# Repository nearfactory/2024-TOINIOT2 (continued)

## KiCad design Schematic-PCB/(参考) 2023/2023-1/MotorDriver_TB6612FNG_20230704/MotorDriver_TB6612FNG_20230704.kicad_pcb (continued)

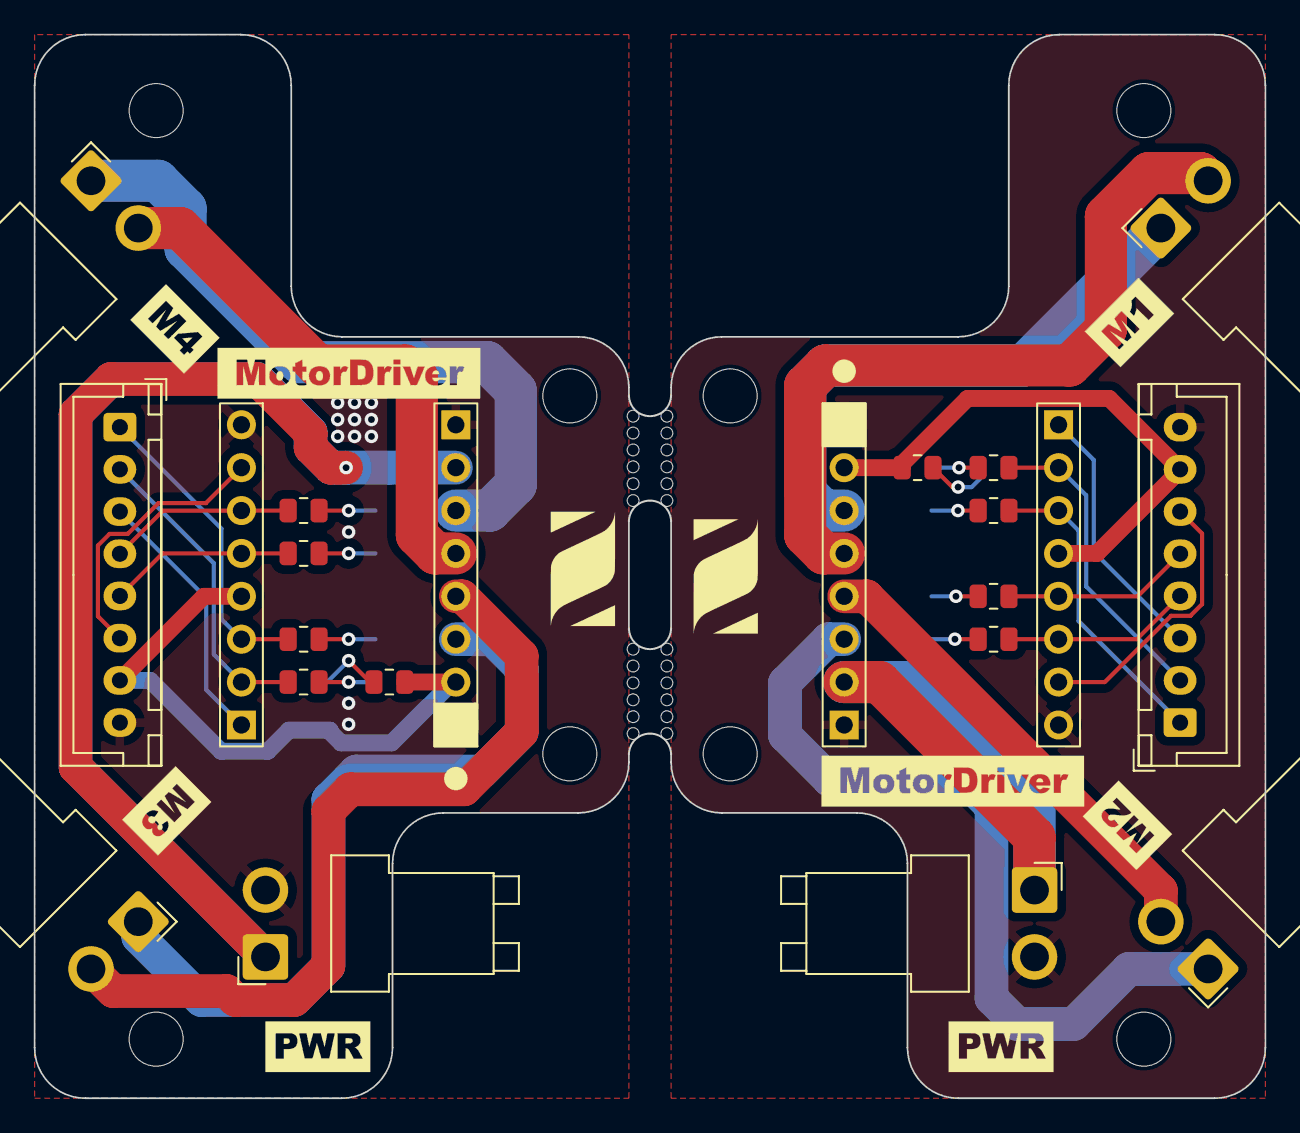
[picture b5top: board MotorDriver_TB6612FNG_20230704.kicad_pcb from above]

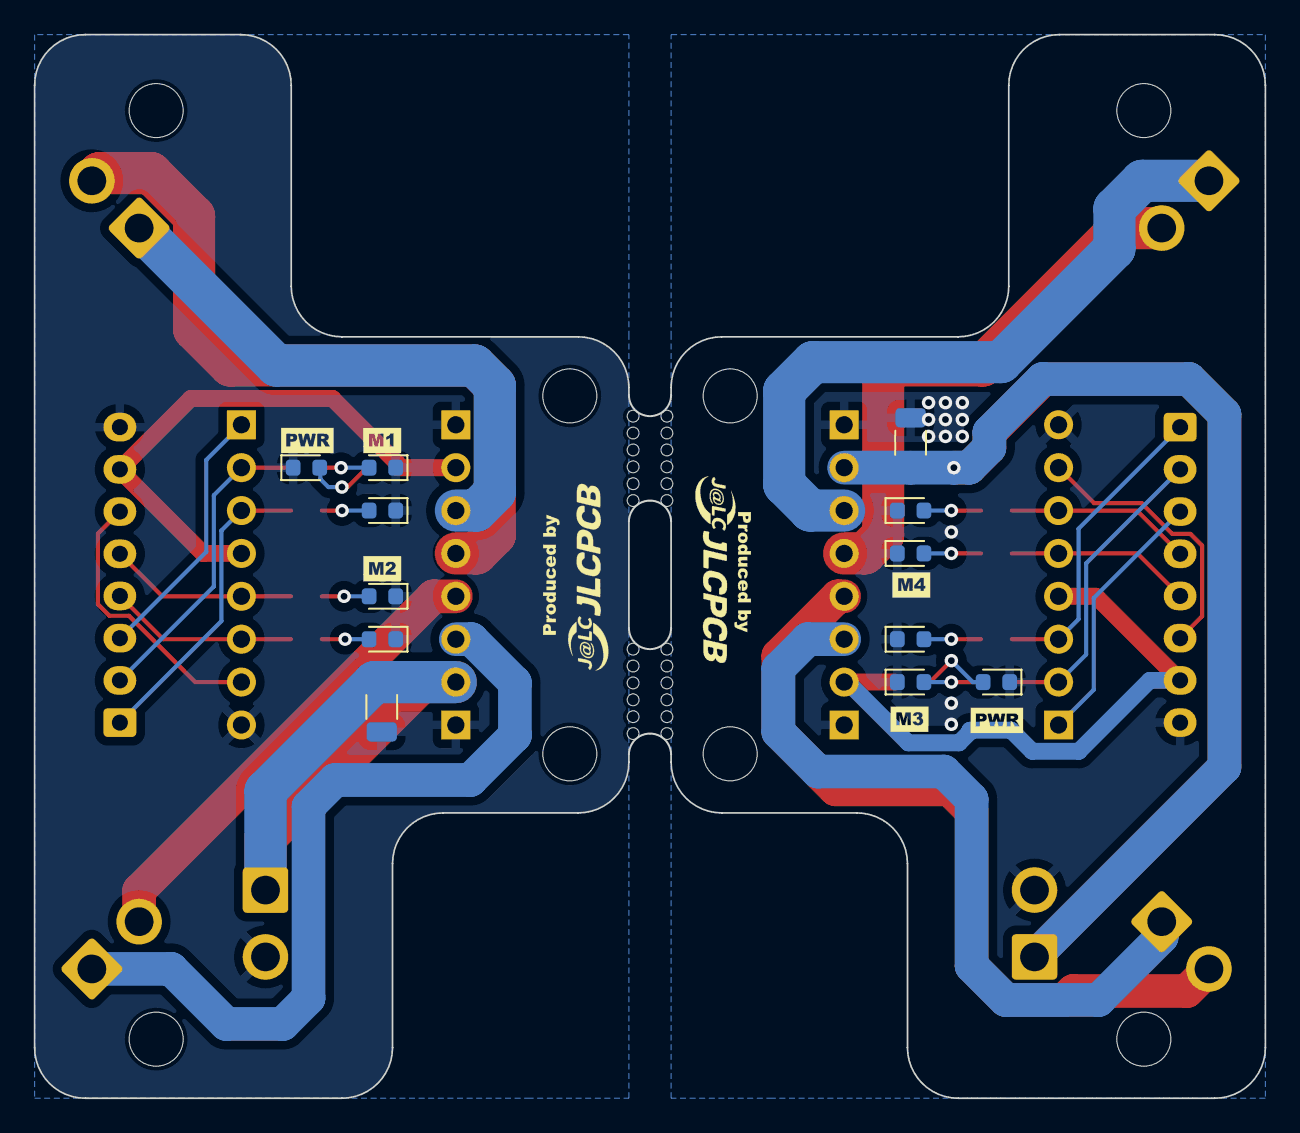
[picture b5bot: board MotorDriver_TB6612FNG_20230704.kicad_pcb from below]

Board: 2 copper layers, 72.9 x 63.0 mm, 32 parts (12 on the bottom side), 35 nets.

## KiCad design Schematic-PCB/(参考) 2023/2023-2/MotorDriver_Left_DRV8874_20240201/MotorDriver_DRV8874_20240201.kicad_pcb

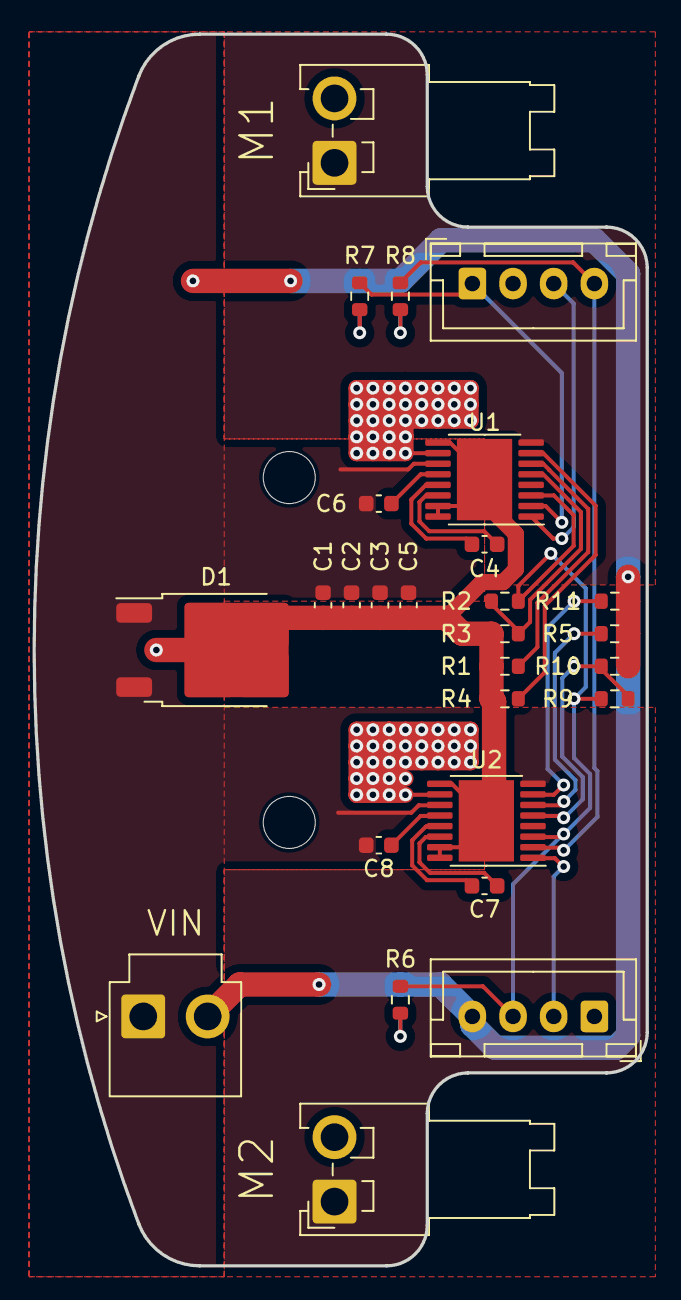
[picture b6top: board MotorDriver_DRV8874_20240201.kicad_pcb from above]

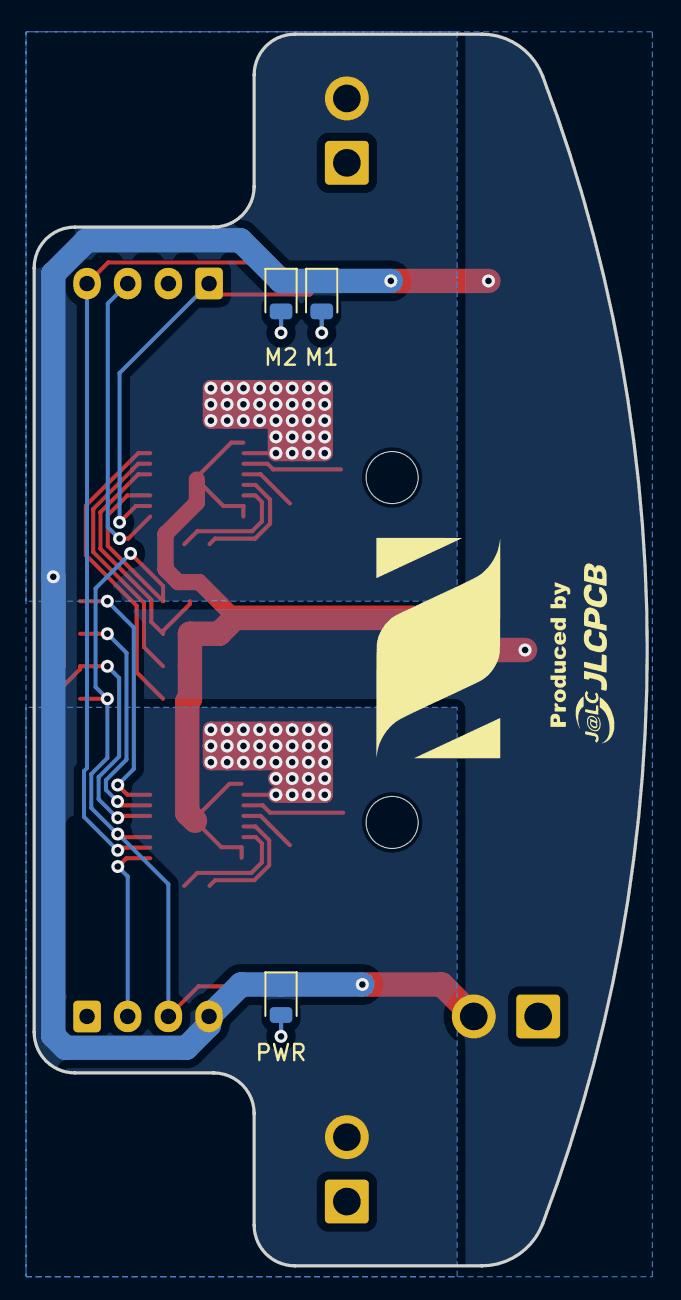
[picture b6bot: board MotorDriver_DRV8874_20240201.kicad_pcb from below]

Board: 2 copper layers, 37.7 x 75.7 mm, 30 parts (3 on the bottom side), 26 nets.

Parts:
C1, C2: 4.7uF; C_0603_1608Metric
C3, C5: 0.1uF; C_0603_1608Metric
C4, C7: 22nF; C_0603_1608Metric
C6, C8: 220nF; C_0603_1608Metric
D1: D_Schottky_AKA; TO-252-2
J4, J5: Conn_01x04_Pin; JST_XH_B4B-XH-A_1x04_P2.50mm_Vertical
M1, M2: Conn_01x02_Pin; JST_VH_S2P-VH_1x02_P3.96mm_Horizontal
M1#2, M2#2: LED; LED_0805_2012Metric
PWR: LED; LED_0805_2012Metric
R1, R5: 2.49K; R_0603_1608Metric
R2, R9: 10K; R_0603_1608Metric
R3, R10: NP; R_0603_1608Metric
R4, R11: 20K; R_0603_1608Metric
R6, R7, R8: 330; R_0603_1608Metric
U1, U2: HTSSOP-16-1EP_4.4x5mm_P0.65mm_EP3.4x5mm_Mask2.46x2.31mm_The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
VIN: Conn_01x02_Pin; JST_VH_B2P-VH-B_1x02_P3.96mm_Vertical

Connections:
EN-1: J4.3, U1.1 (EN)
EN-2: J5.2, U2.1 (EN)
GND: C1.2, C2.2, C3.2, C5.2, D1.2 (K), J5.4, M1#2.1 (K), M2#2.1 (K), PWR.1 (K), R1.1, R3.2, R4.2, R5.1, R10.2, R11.2, U1.9 (PGND), U1.15 (GND), U1.16 (PMODE), U1.17 (PAD), U2.9 (PGND), U2.15 (GND), U2.16 (PMODE), U2.17 (PAD), VIN.2
IMODE-1: R4.1, U1.7 (IMODE)
IMODE-2: R11.1, U2.7 (IMODE)
unnamed: PWR.2 (A), R6.2
unnamed: M1#2.2 (A), R7.2
unnamed: M2#2.2 (A), R8.2
unnamed: C4.2, U1.13 (CPH)
unnamed: C4.1, U1.14 (CPL)
unnamed: R1.2, U1.6 (IPROPI)
unnamed: C6.1, U1.12 (VCP)
unnamed: C7.2, U2.13 (CPH)
unnamed: C7.1, U2.14 (CPL)
unnamed: R5.2, U2.6 (IPROPI)
unnamed: C8.1, U2.12 (VCP)
OUT1-1: M1.1, U1.8 (OUT1)
OUT1-2: M2.1, U2.8 (OUT1)
OUT2-1: M1.2, U1.10 (OUT2)
OUT2-2: M2.2, U2.10 (OUT2)
PH-1: J4.1, R7.1, U1.2 (PH)
PH-2: J4.4, R8.1, U2.2 (PH)
SLEEP-1: J5.3, R2.1, R6.1, R9.1, U1.3 (SLEEP), U2.3 (SLEEP)
VIN: C1.1, C2.1, C3.1, C5.1, C6.2, C8.2, D1.1 (A), D1.3 (A), U1.11 (VM), U2.11 (VM), VIN.1
VREF-1: R2.2, R3.1, U1.5 (VREF)
VREF-2: R9.2, R10.1, U2.5 (VREF)

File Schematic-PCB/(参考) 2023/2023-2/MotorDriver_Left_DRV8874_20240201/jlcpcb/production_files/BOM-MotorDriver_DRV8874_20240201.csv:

Comment,Designator,Footprint,LCSC
0.1uF,"C3,C5",C_0603_1608Metric,C14663
~,"U1,U2",HTSSOP-16-1EP_4.4x5mm_P0.65mm_EP3.4x5mm_Mask2.46x2.31mm_ThermalVias,C1855818
4.7uF,"C1,C2",C_0603_1608Metric,C19666
220nF,"C6,C8",C_0603_1608Metric,C21120
22nF,"C4,C7",C_0603_1608Metric,C21122
2.49K,"R1,R5",R_0603_1608Metric,C22908
330,"R6,R7,R8",R_0603_1608Metric,C23138
10K,"R2,R9",R_0603_1608Metric,C25804
20K,"R11,R4",R_0603_1608Metric,C4184
D_Schottky_AKA,D1,TO-252-2,C668192
LED,M1,LED_0805_2012Metric,
LED,M2,LED_0805_2012Metric,
